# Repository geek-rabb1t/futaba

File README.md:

# Futaba

Futaba is a keyboard with trackpad.

## Features

- One-step-down thumb cluster that reduces fatigue even after long hours of work.
- Trackpad with multi-touch support for up to four fingers.
- Clickable giant wheel.
- Stack-mounted and flex-cut for the same feel on every key.
- Cable guides for easy use in tight spaces.

## Directory structure

This repository contains hardware design data only.

- Cases
    - 3D data of cases designed with FreeCAD.
    - It also contains stl files.
- Forms
    - Cut data of forms designed in Affinity Designer that can be ordered from Yousha Kobo.
- PCB
    - PCB data designed by KiCAD.

## About Firmware

QMK firmware or Vial firmware can be obtained from the following URL

- QMK Firmware
  - https://github.com/geek-rabb1t/qmk_firmware/tree/futaba
- Vial
  - https://github.com/geek-rabb1t/vial-qmk/tree/gr_master/keyboards/geek_rabb1t/futaba

## Build Guide

Please read here.

- https://geek-rabb1t.github.io/futaba/build_guide

---

# Futaba

Futabaはトラックパッド付きキーボードです。

## 特徴

- 長時間の作業でも疲れにくい、一段下がった親指クラスタ。
- 4本指までのマルチタッチに対応したトラックパッド。
- クリック可能な巨大ホイール。
- スタックマウントとフレックスカットにより、どのキーも同じ打鍵感。
- 狭い場所でも使いやすいケーブルガイド。

## ディレクトリ構造

このリポジトリにはハードウェアの設計データのみ格納しています。

- case
    - FreeCADで設計したケースの3Dデータ。
    - stlファイルも含まれます。
- form
    - Affinity designerで設計した遊舎工房に発注可能なFormのカットデータ。
- pcb
    - KiCADで設計したPCBデータ。

## ファームウェアについて

以下のURLにQMK Firmwareもしくは、 Vialのファームウェアがあります。

- QMK Firmware
  - https://github.com/geek-rabb1t/qmk_firmware/tree/futaba
- Vial
  - https://github.com/geek-rabb1t/vial-qmk/tree/gr_master/keyboards/geek_rabb1t/futaba

## 組み立て手順

こちらをご覧ください。

- https://geek-rabb1t.github.io/futaba/build_guide

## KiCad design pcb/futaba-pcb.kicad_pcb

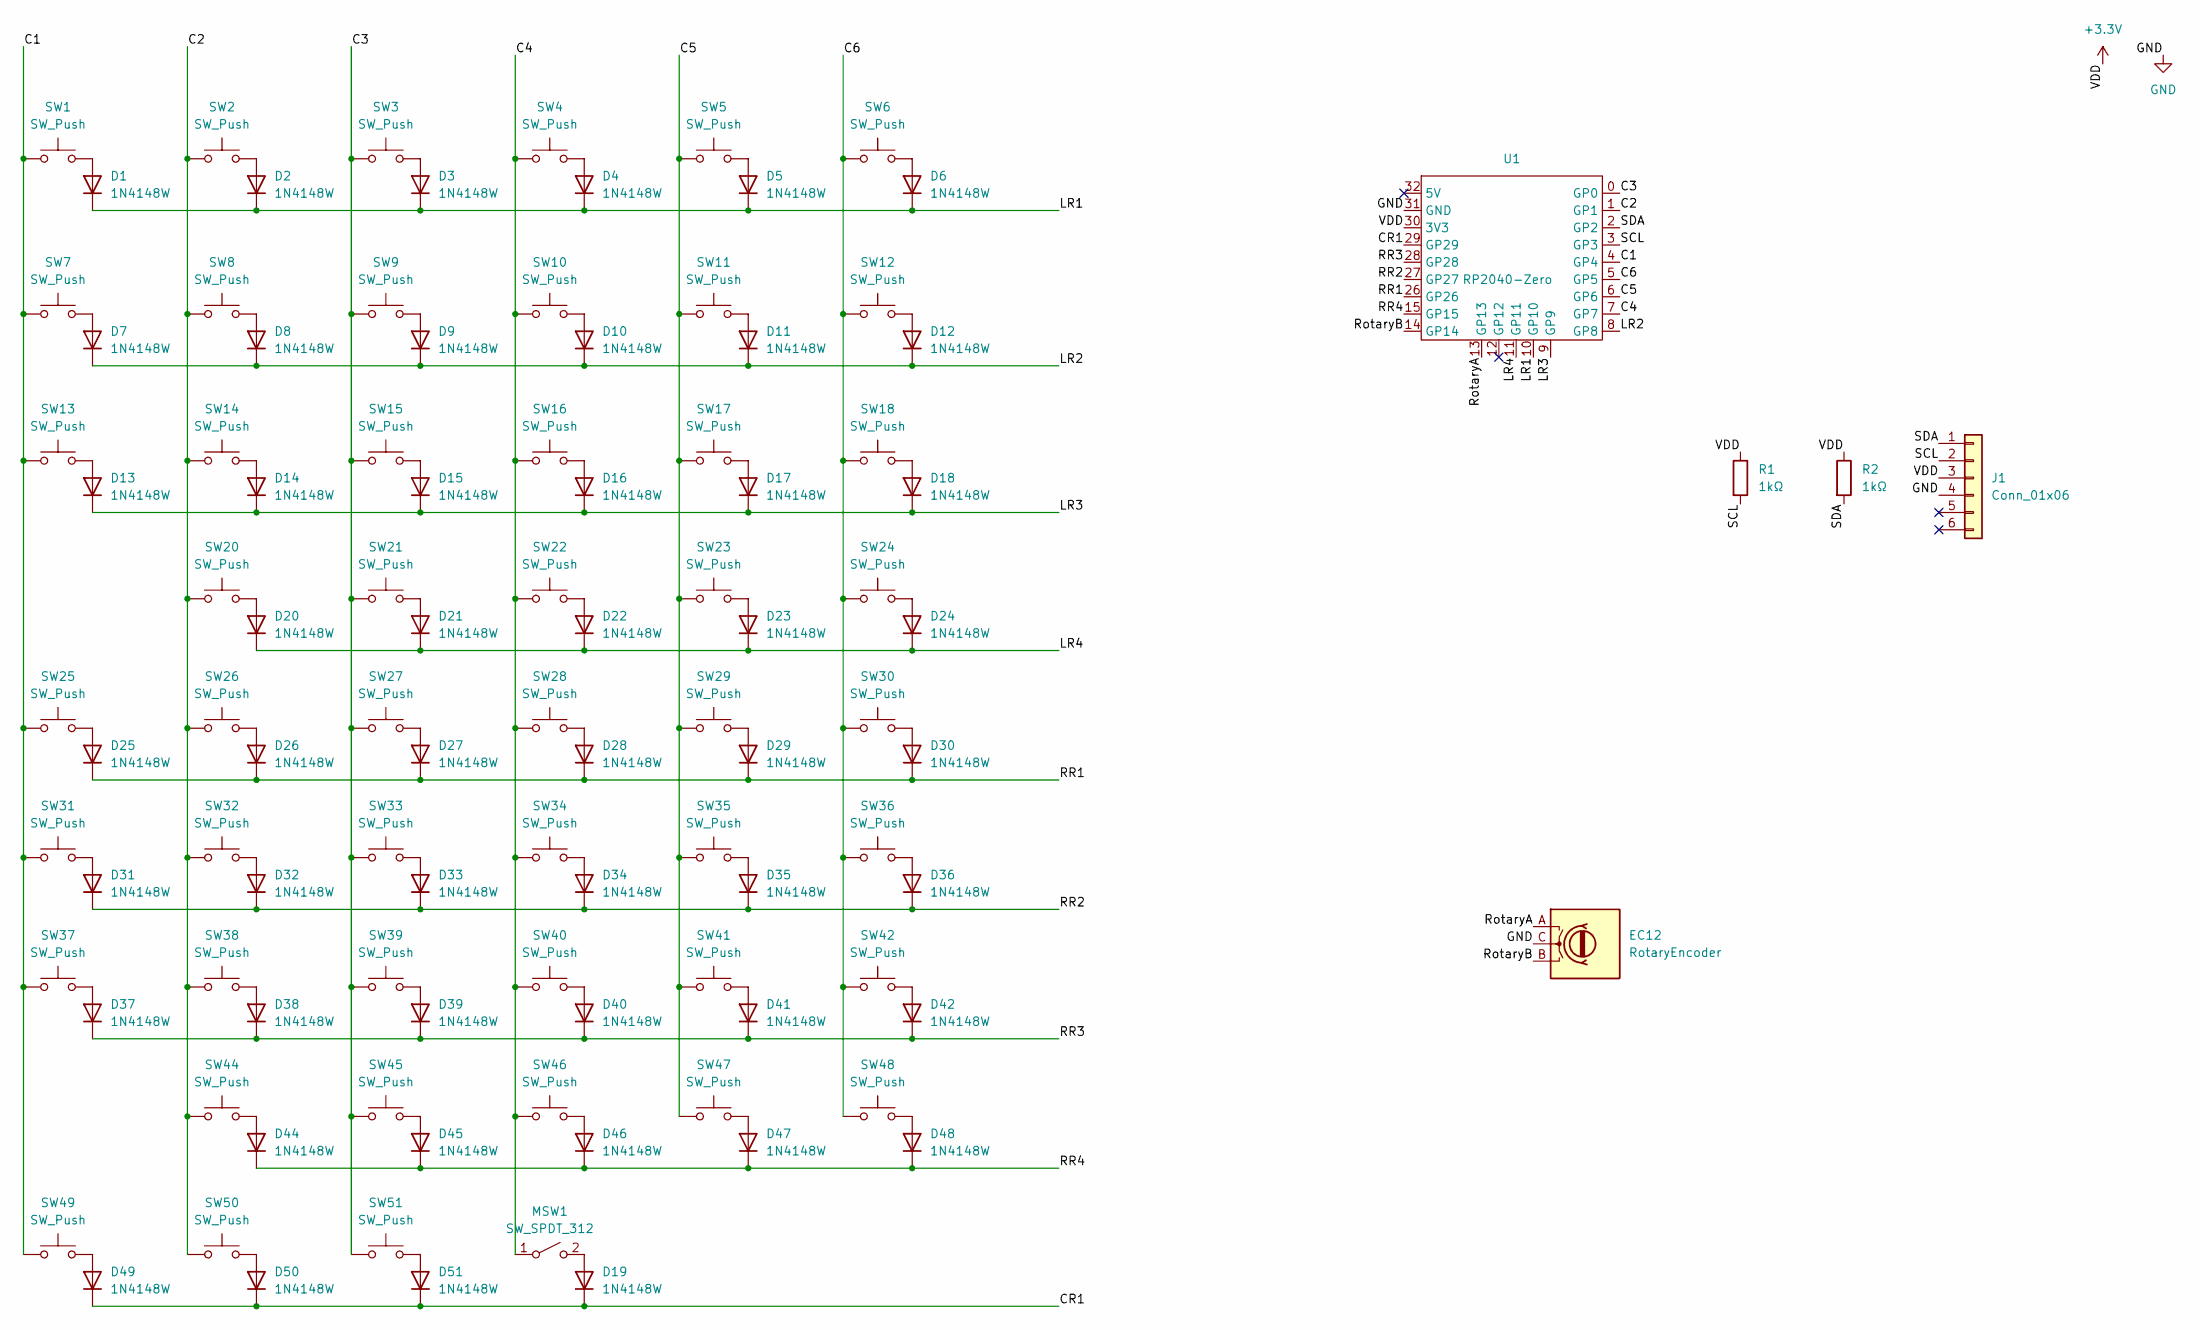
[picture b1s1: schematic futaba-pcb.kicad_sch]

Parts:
D1, D2, D3, D4, D5, D6, D7, D8, D9, D10, D11, D12, D13, D14, D15, D16, D17, D18, D19, D20, D21, D22, D23, D24, D25, D26, D27, D28, D29, D30, D31, D32, D33, D34, D35, D36, D37, D38, D39, D40, D41, D42, D44, D45, D46, D47, D48, D49, D50, D51: 1N4148W; D_SOD-123
EC12: RotaryEncoder; RotaryEncoder_Alps_EC12E_Vertical_H20mm
J1: Conn_01x06; Jushuo_AFC07-S06FCA-00_1x6-1MP_P0.50_Horizontal-JLC; LCSC Part # C11048
MSW1: SW_SPDT_312; MicroSwitch; Part Name D2F-01FL2-A
R1, R2: 1kΩ; R_0603_1608Metric
SW1, SW2, SW3, SW4, SW5, SW6, SW25, SW26, SW27, SW28, SW29, SW30, SW49, SW50, SW51: SW_Push; Choc_Socket-flex-drill_top
SW7, SW8, SW9, SW10, SW11, SW12, SW13, SW14, SW15, SW16, SW17, SW18, SW31, SW32, SW33, SW34, SW35, SW36, SW37, SW38, SW39, SW40, SW41: SW_Push; Choc_Socket-flex-drill
SW20, SW21, SW42, SW44, SW45: SW_Push; Choc_Socket-flex-drill_bottom
SW22, SW23, SW24, SW46, SW47, SW48: SW_Push; Choc_Socket-flex-drill_mid
U1: RP2040-Zero

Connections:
+3.3V: J1.3, R1.1, R2.1, U1.30 (3V3)
/C1: SW1.1, SW7.1, SW13.1, SW25.1, SW31.1, SW37.1, SW49.1, U1.4 (GP4)
/C2: SW2.1, SW8.1, SW14.1, SW20.1, SW26.1, SW32.1, SW38.1, SW44.1, SW50.1, U1.1 (GP1)
/C3: SW3.1, SW9.1, SW15.1, SW21.1, SW27.1, SW33.1, SW39.1, SW45.1, SW51.1, U1.0 (GP0)
/C4: MSW1.1 (A), SW4.1, SW10.1, SW16.1, SW22.1, SW28.1, SW34.1, SW40.1, SW46.1, U1.7 (GP7)
/C5: SW5.1, SW11.1, SW17.1, SW23.1, SW29.1, SW35.1, SW41.1, SW47.1, U1.6 (GP6)
/C6: SW6.1, SW12.1, SW18.1, SW24.1, SW30.1, SW36.1, SW42.1, SW48.1, U1.5 (GP5)
/CR1: D19.1 (K), D49.1 (K), D50.1 (K), D51.1 (K), U1.29 (GP29)
/LR1: D1.1 (K), D2.1 (K), D3.1 (K), D4.1 (K), D5.1 (K), D6.1 (K), U1.10 (GP10)
/LR2: D7.1 (K), D8.1 (K), D9.1 (K), D10.1 (K), D11.1 (K), D12.1 (K), U1.8 (GP8)
/LR3: D13.1 (K), D14.1 (K), D15.1 (K), D16.1 (K), D17.1 (K), D18.1 (K), U1.9 (GP9)
/LR4: D20.1 (K), D21.1 (K), D22.1 (K), D23.1 (K), D24.1 (K), U1.11 (GP11)
/RR1: D25.1 (K), D26.1 (K), D27.1 (K), D28.1 (K), D29.1 (K), D30.1 (K), U1.26 (GP26)
/RR2: D31.1 (K), D32.1 (K), D33.1 (K), D34.1 (K), D35.1 (K), D36.1 (K), U1.27 (GP27)
/RR3: D37.1 (K), D38.1 (K), D39.1 (K), D40.1 (K), D41.1 (K), D42.1 (K), U1.28 (GP28)
/RR4: D44.1 (K), D45.1 (K), D46.1 (K), D47.1 (K), D48.1 (K), U1.15 (GP15)
/RotaryA: EC12.A, U1.13 (GP13)
/RotaryB: EC12.B, U1.14 (GP14)
/SCL: J1.2, R1.2, U1.3 (GP3)
/SDA: J1.1, R2.2, U1.2 (GP2)
GND: EC12.C, J1.4, U1.31 (GND)
unnamed: D1.2 (A), SW1.2
unnamed: D2.2 (A), SW2.2
unnamed: D3.2 (A), SW3.2
unnamed: D4.2 (A), SW4.2
unnamed: D5.2 (A), SW5.2
unnamed: D6.2 (A), SW6.2
unnamed: D7.2 (A), SW7.2
unnamed: D8.2 (A), SW8.2
unnamed: D9.2 (A), SW9.2
unnamed: D10.2 (A), SW10.2
unnamed: D11.2 (A), SW11.2
unnamed: D12.2 (A), SW12.2
unnamed: D13.2 (A), SW13.2
unnamed: D14.2 (A), SW14.2
unnamed: D15.2 (A), SW15.2
unnamed: D16.2 (A), SW16.2
unnamed: D17.2 (A), SW17.2
unnamed: D18.2 (A), SW18.2
unnamed: D19.2 (A), MSW1.2 (B)
unnamed: D20.2 (A), SW20.2
unnamed: D21.2 (A), SW21.2
unnamed: D22.2 (A), SW22.2
unnamed: D23.2 (A), SW23.2
unnamed: D24.2 (A), SW24.2
unnamed: D25.2 (A), SW25.2
unnamed: D26.2 (A), SW26.2
unnamed: D27.2 (A), SW27.2
unnamed: D28.2 (A), SW28.2
unnamed: D29.2 (A), SW29.2
unnamed: D30.2 (A), SW30.2
unnamed: D31.2 (A), SW31.2
unnamed: D32.2 (A), SW32.2
unnamed: D33.2 (A), SW33.2
unnamed: D34.2 (A), SW34.2
unnamed: D35.2 (A), SW35.2
unnamed: D36.2 (A), SW36.2
unnamed: D37.2 (A), SW37.2
unnamed: D38.2 (A), SW38.2
unnamed: D39.2 (A), SW39.2
unnamed: D40.2 (A), SW40.2
unnamed: D41.2 (A), SW41.2
unnamed: D42.2 (A), SW42.2
unnamed: D44.2 (A), SW44.2
unnamed: D45.2 (A), SW45.2
unnamed: D46.2 (A), SW46.2
unnamed: D47.2 (A), SW47.2
unnamed: D48.2 (A), SW48.2
unnamed: D49.2 (A), SW49.2
unnamed: D50.2 (A), SW50.2
unnamed: D51.2 (A), SW51.2

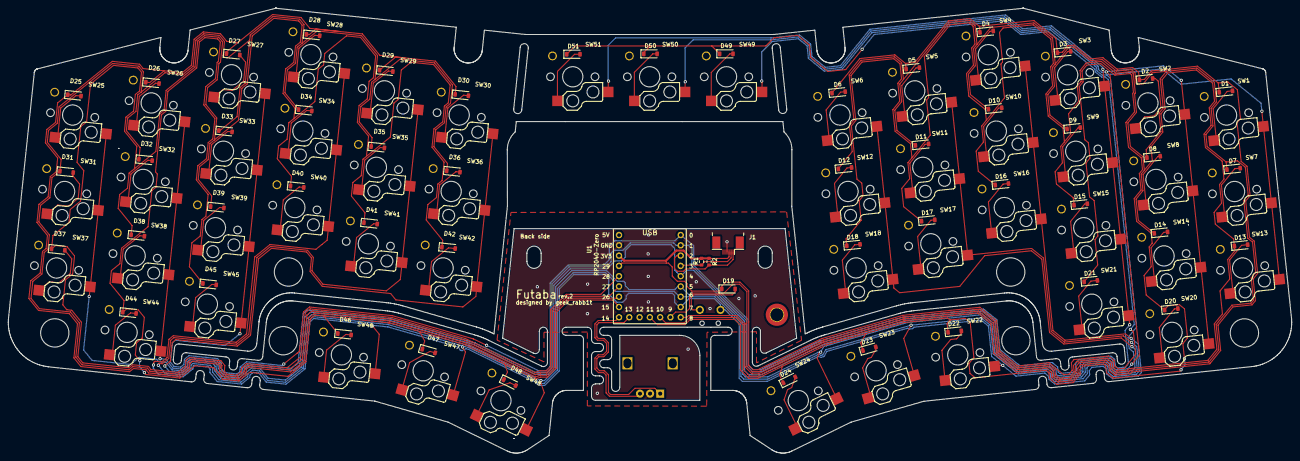
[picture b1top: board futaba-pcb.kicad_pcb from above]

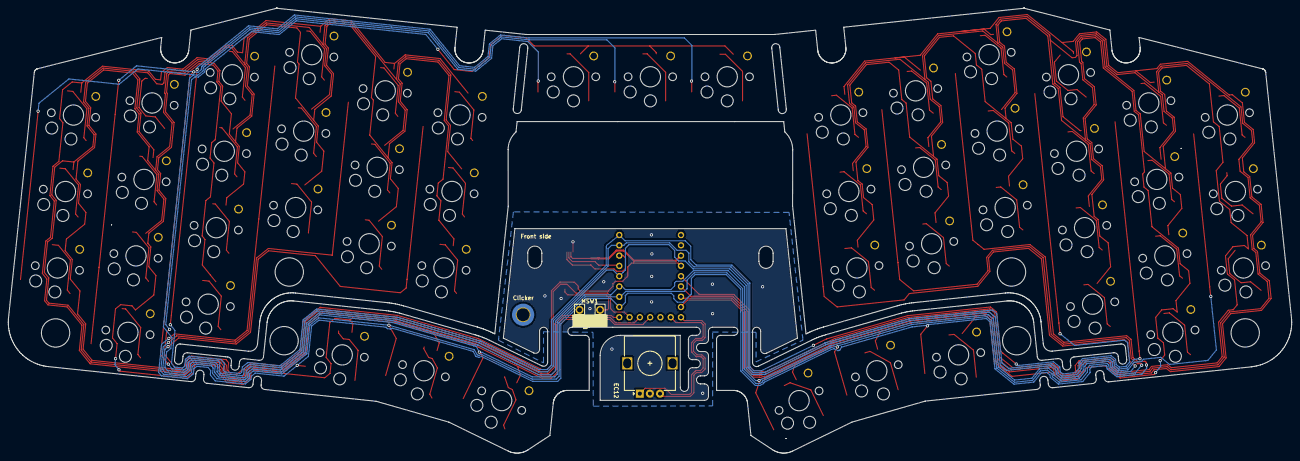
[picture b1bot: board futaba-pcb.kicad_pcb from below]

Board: 2 copper layers, 317.0 x 109.8 mm, 106 parts (2 on the bottom side), 71 nets.

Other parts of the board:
Clicker: MountingHole_3.2mm_M3_ISO14580_Pad_TopBottom

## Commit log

2023-12-19 add ignore files
2024-07-26 update 3d model
2024-07-26 add form cutting data
2024-07-26 Add kicad data
2024-08-25 Update pcb data
2024-08-25 add logo
2024-11-13 move pcb folder
2024-11-13 Update form laser cutting data
2024-11-13 Change logo data
2024-11-13 Update case data
2024-11-19 Update case data.
2024-11-19 Update form data.
2024-11-19 Update pcb outline.
2025-01-11 Remove duplicate paths
2025-01-11 Update case design
2025-03-02 add firmware binary
2025-03-02 Fix bottom of case
2025-03-16 update clicker
2025-05-31 add soldering jig
2025-06-27 Create geek_rabb1t_futaba_vial-v2-beta.uf2
    https://github.com/geek-rabb1t/vial-qmk/tree/9ec0be02f3425786703334e832c7dbf1c5a1e68f
2025-07-05 update firmware
2026-04-01 improve clicker for fdm
2026-04-01 add microswitch adapter
2026-04-01 update pcb
